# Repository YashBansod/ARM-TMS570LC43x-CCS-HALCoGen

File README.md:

# ARM-TMS570LC43x-CCS-HALCoGen
This repository contains all my practice codes/projects of Hercules TMS570LC43x Development Kit. The projects are made using embedded C on CCS 6 and HALCoGen.

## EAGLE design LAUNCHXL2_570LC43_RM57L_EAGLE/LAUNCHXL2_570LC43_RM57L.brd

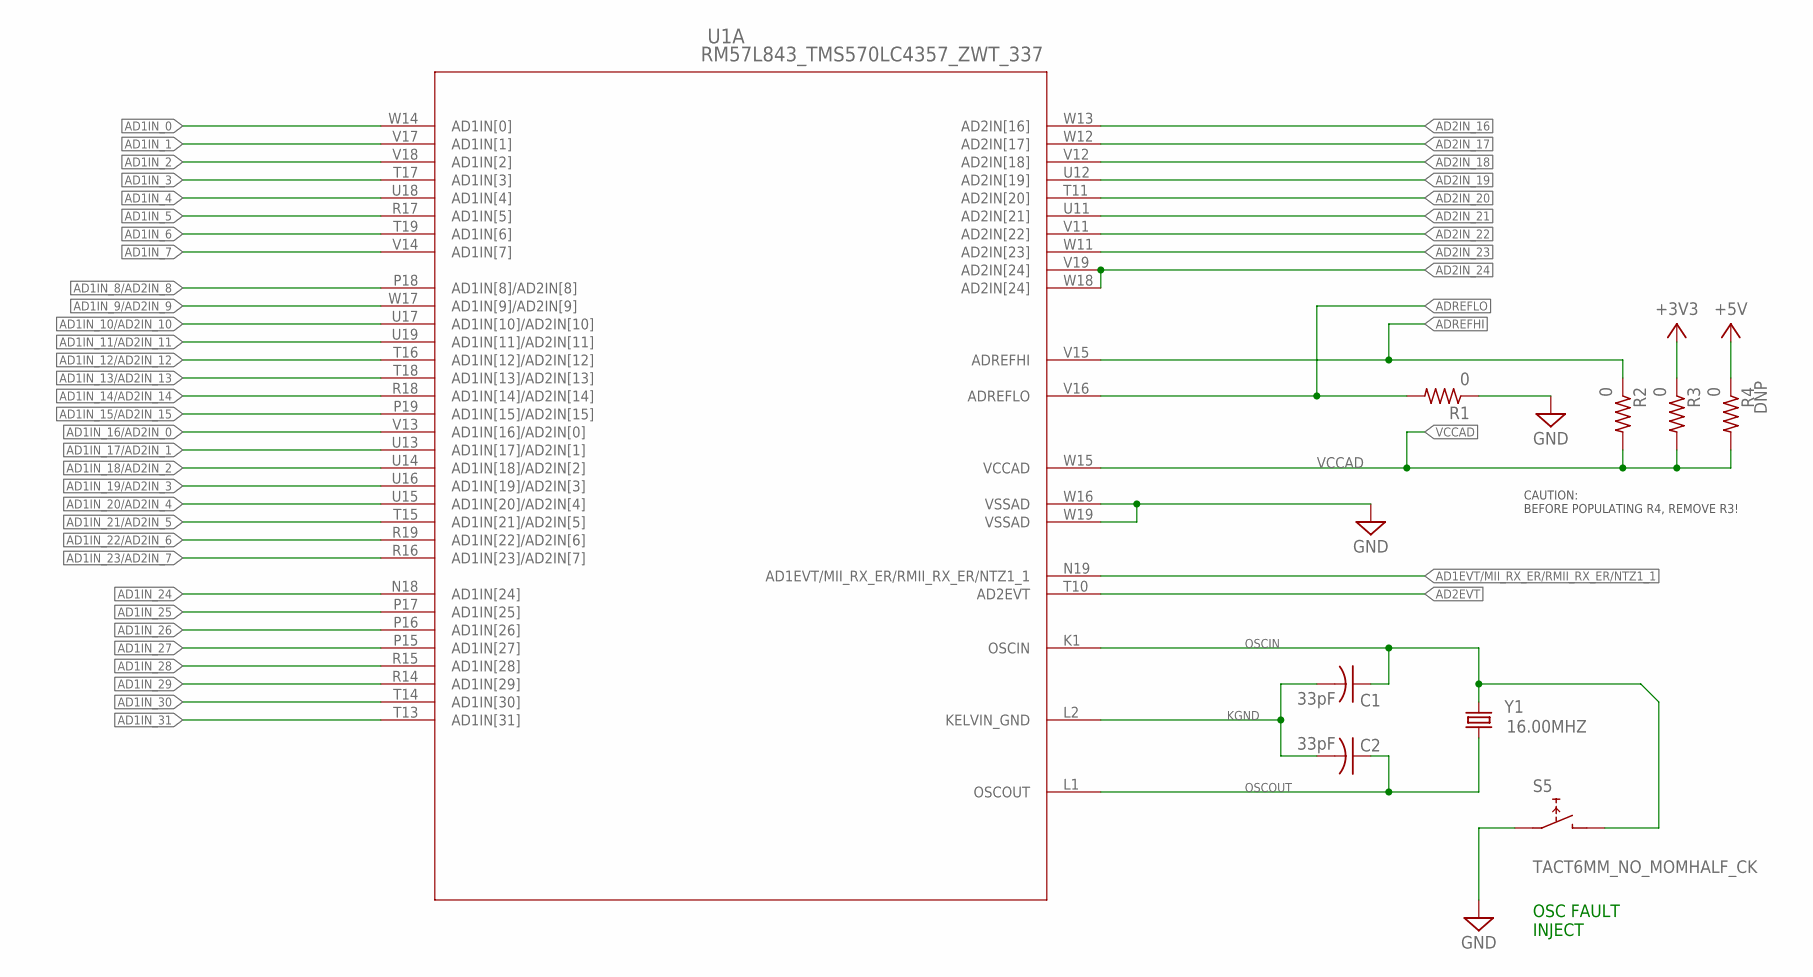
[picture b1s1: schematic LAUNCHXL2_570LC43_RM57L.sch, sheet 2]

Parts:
C1, C2: 33pF; C0201; PARTNO CC0201JRNPO8BN330
R1, R2, R3, R4: 0; R0201; PARTNO RC0201JR-070RL
S5: TACT6MM_NO_MOMHALF_CK; CK_PTS645_SMD; PARTNO PTS645SM43SMTR92 LFS
U1: RM57L843_TMS570LC4357_ZWT_337; ZWT337; PARTNO TMP5704357AZWTQQ1
Y1: 16.00MHZ; CSM-3X; PARTNO ECS-160-20-3X-TR

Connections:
+3V3: R3.1; also elsewhere on the board
+5V: R4.1; also elsewhere on the board
AD1EVT/MII_RX_ER/RMII_RX_ER/NTZ1_1: U1.N19 (AD1EVT/MII_RX_ER/RMII_RX_ER/NTZ1_1); also elsewhere on the board
AD1IN_0: U1.W14 (AD1IN[0]); also elsewhere on the board
AD1IN_1: U1.V17 (AD1IN[1]); also elsewhere on the board
AD1IN_2: U1.V18 (AD1IN[2]); also elsewhere on the board
AD1IN_3: U1.T17 (AD1IN[3]); also elsewhere on the board
AD1IN_4: U1.U18 (AD1IN[4]); also elsewhere on the board
AD1IN_5: U1.R17 (AD1IN[5]); also elsewhere on the board
AD1IN_6: U1.T19 (AD1IN[6]); also elsewhere on the board
AD1IN_7: U1.V14 (AD1IN[7]); also elsewhere on the board
AD1IN_8/AD2IN_8: U1.P18 (AD1IN[8]/AD2IN[8]); also elsewhere on the board
AD1IN_9/AD2IN_9: U1.W17 (AD1IN[9]/AD2IN[9]); also elsewhere on the board
AD1IN_10/AD2IN_10: U1.U17 (AD1IN[10]/AD2IN[10]); also elsewhere on the board
AD1IN_11/AD2IN_11: U1.U19 (AD1IN[11]/AD2IN[11]); also elsewhere on the board
AD1IN_12/AD2IN_12: U1.T16 (AD1IN[12]/AD2IN[12]); also elsewhere on the board
AD1IN_13/AD2IN_13: U1.T18 (AD1IN[13]/AD2IN[13]); also elsewhere on the board
AD1IN_14/AD2IN_14: U1.R18 (AD1IN[14]/AD2IN[14]); also elsewhere on the board
AD1IN_15/AD2IN_15: U1.P19 (AD1IN[15]/AD2IN[15]); also elsewhere on the board
AD1IN_16/AD2IN_0: U1.V13 (AD1IN[16]/AD2IN[0]); also elsewhere on the board
AD1IN_17/AD2IN_1: U1.U13 (AD1IN[17]/AD2IN[1]); also elsewhere on the board
AD1IN_18/AD2IN_2: U1.U14 (AD1IN[18]/AD2IN[2]); also elsewhere on the board
AD1IN_19/AD2IN_3: U1.U16 (AD1IN[19]/AD2IN[3]); also elsewhere on the board
AD1IN_20/AD2IN_4: U1.U15 (AD1IN[20]/AD2IN[4]); also elsewhere on the board
AD1IN_21/AD2IN_5: U1.T15 (AD1IN[21]/AD2IN[5]); also elsewhere on the board
AD1IN_22/AD2IN_6: U1.R19 (AD1IN[22]/AD2IN[6]); also elsewhere on the board
AD1IN_23/AD2IN_7: U1.R16 (AD1IN[23]/AD2IN[7]); also elsewhere on the board
AD1IN_24: U1.N18 (AD1IN[24]); also elsewhere on the board
AD1IN_25: U1.P17 (AD1IN[25]); also elsewhere on the board
AD1IN_26: U1.P16 (AD1IN[26]); also elsewhere on the board
AD1IN_27: U1.P15 (AD1IN[27]); also elsewhere on the board
AD1IN_28: U1.R15 (AD1IN[28]); also elsewhere on the board
AD1IN_29: U1.R14 (AD1IN[29]); also elsewhere on the board
AD1IN_30: U1.T14 (AD1IN[30]); also elsewhere on the board
AD1IN_31: U1.T13 (AD1IN[31]); also elsewhere on the board
AD2EVT: U1.T10 (AD2EVT); also elsewhere on the board
AD2IN_16: U1.W13 (AD2IN[16]); also elsewhere on the board
AD2IN_17: U1.W12 (AD2IN[17]); also elsewhere on the board
AD2IN_18: U1.V12 (AD2IN[18]); also elsewhere on the board
AD2IN_19: U1.U12 (AD2IN[19]); also elsewhere on the board
AD2IN_20: U1.T11 (AD2IN[20]); also elsewhere on the board
AD2IN_21: U1.U11 (AD2IN[21]); also elsewhere on the board
AD2IN_22: U1.V11 (AD2IN[22]); also elsewhere on the board
AD2IN_23: U1.W11 (AD2IN[23]); also elsewhere on the board
AD2IN_24: U1.V19 (AD2IN[24]), U1.W18 (AD2IN[24]); also elsewhere on the board
ADREFHI: R2.1, U1.V15 (ADREFHI); also elsewhere on the board
ADREFLO: R1.2, U1.V16 (ADREFLO); also elsewhere on the board
GND: R1.1, S5.1 (12), U1.W16 (VSSAD), U1.W19 (VSSAD); also elsewhere on the board
KGND: C1.2, C2.2, U1.L2 (KELVIN_GND)
OSCIN: C1.1, S5.3 (34), U1.K1 (OSCIN), Y1.2
OSCOUT: C2.1, U1.L1 (OSCOUT), Y1.1
VCCAD: R2.2, R3.2, R4.2, U1.W15 (VCCAD); also elsewhere on the board

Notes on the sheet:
OSC FAULT INJECT
CAUTION: BEFORE POPULATING R4, REMOVE R3!

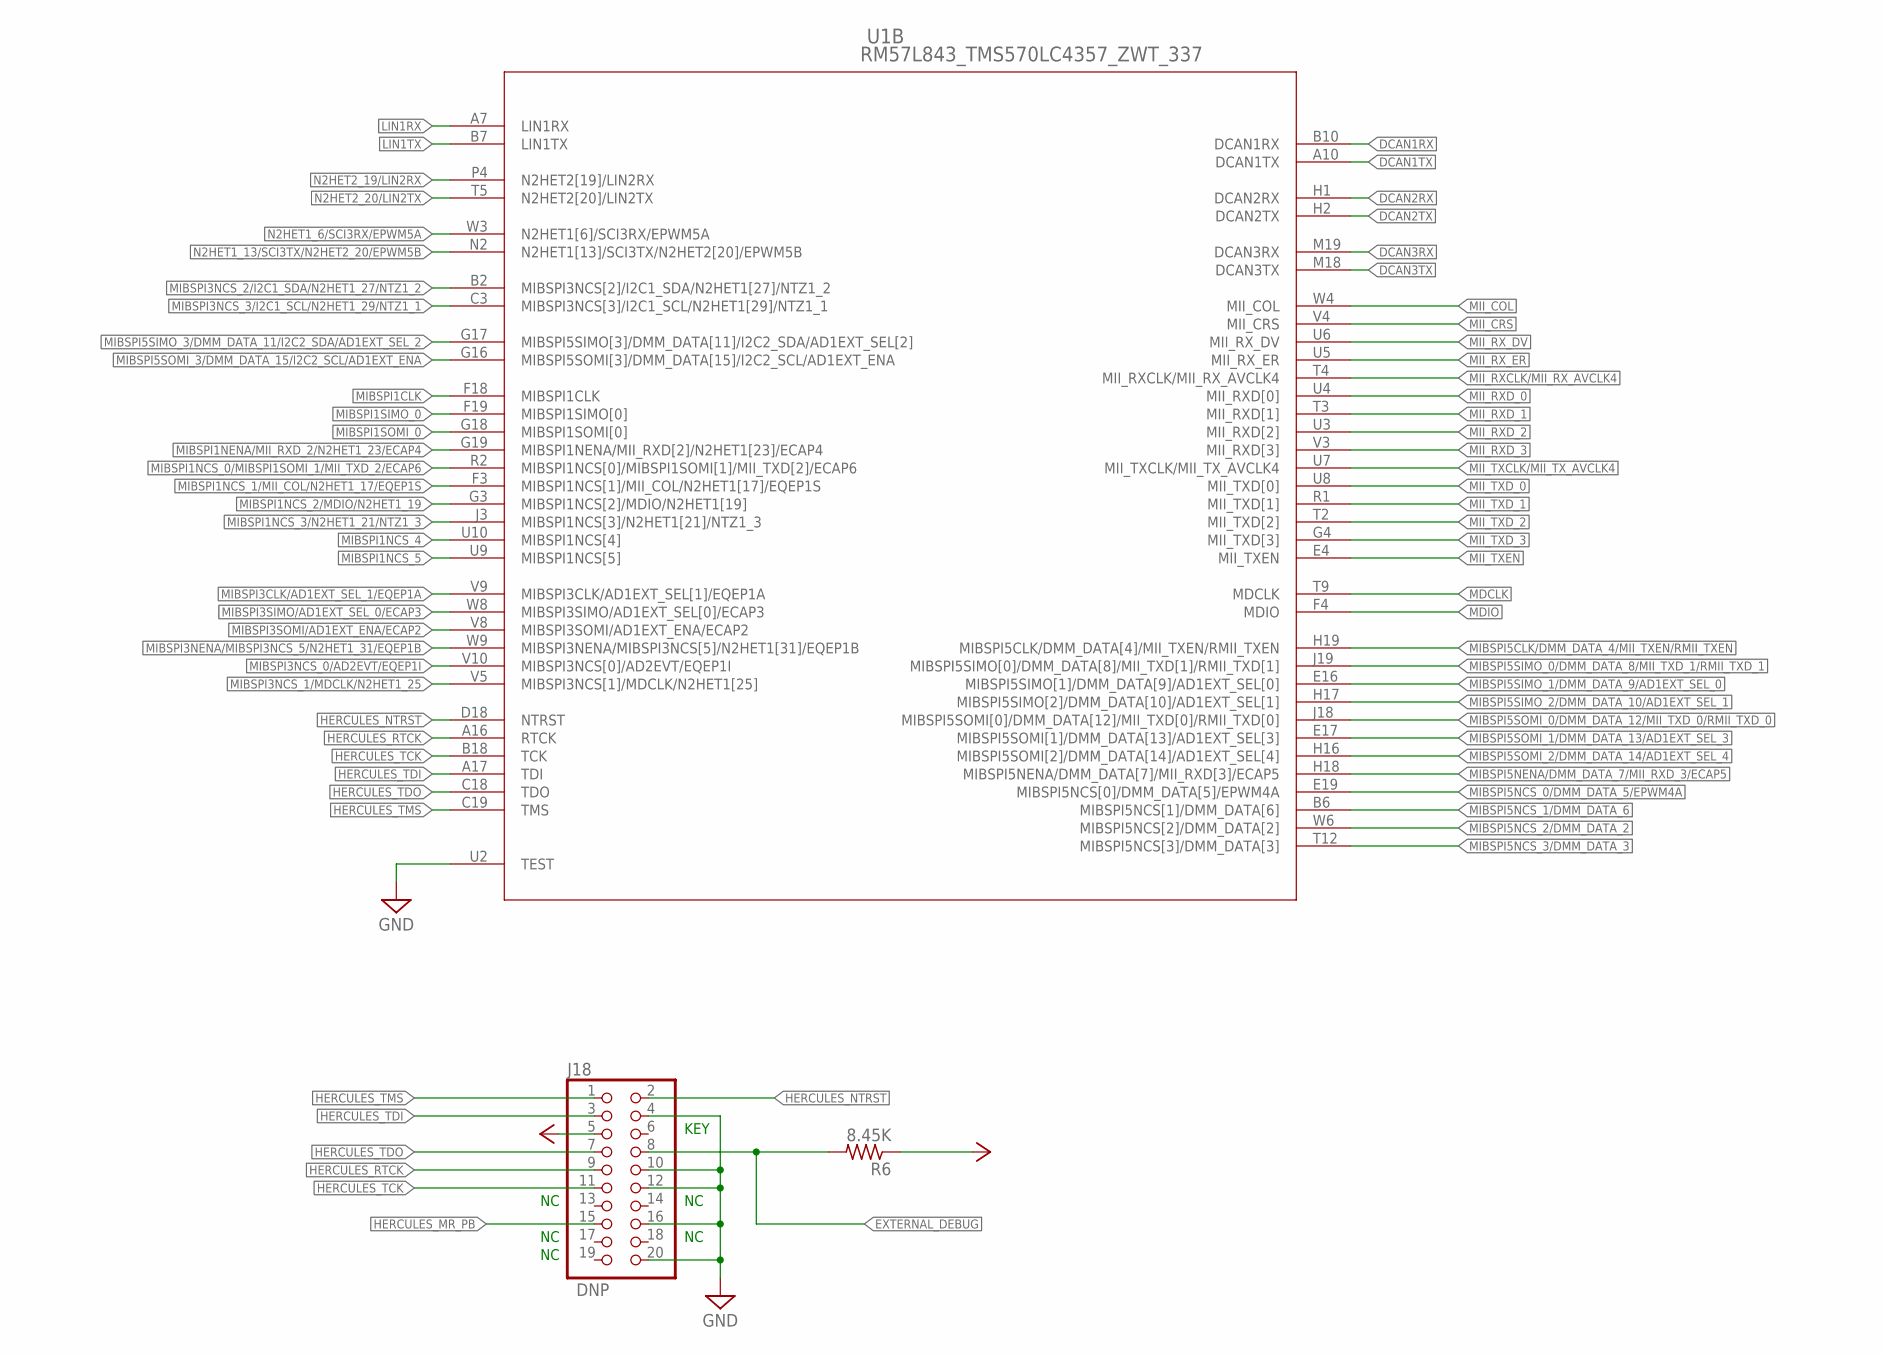
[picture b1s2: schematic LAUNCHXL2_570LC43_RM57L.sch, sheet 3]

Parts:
J18: PINHD-2X10SAMTEC-FTR-110-51-S-D-06; SAMTEC-FTR-110-51-S-D-06; PARTNO FTR-110-51-S-D-06
R6: 8.45K; R0201; PARTNO RC0603F8451CS
U1: RM57L843_TMS570LC4357_ZWT_337; ZWT337; PARTNO TMP5704357AZWTQQ1

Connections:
+3V3: J18.5, R6.1; also elsewhere on the board
DCAN1RX: U1.B10 (DCAN1RX); also elsewhere on the board
DCAN1TX: U1.A10 (DCAN1TX); also elsewhere on the board
DCAN2RX: U1.H1 (DCAN2RX); also elsewhere on the board
DCAN2TX: U1.H2 (DCAN2TX); also elsewhere on the board
DCAN3RX: U1.M19 (DCAN3RX); also elsewhere on the board
DCAN3TX: U1.M18 (DCAN3TX); also elsewhere on the board
EXTERNAL_DEBUG: J18.8, R6.2; also elsewhere on the board
GND: J18.4, J18.10, J18.12, J18.16, J18.20, U1.U2 (TEST); also elsewhere on the board
HERCULES_MR_PB: J18.15; also elsewhere on the board
HERCULES_NTRST: J18.2, U1.D18 (NTRST); also elsewhere on the board
HERCULES_RTCK: J18.9, U1.A16 (RTCK); also elsewhere on the board
HERCULES_TCK: J18.11, U1.B18 (TCK); also elsewhere on the board
HERCULES_TDI: J18.3, U1.A17 (TDI); also elsewhere on the board
HERCULES_TDO: J18.7, U1.C18 (TDO); also elsewhere on the board
HERCULES_TMS: J18.1, U1.C19 (TMS); also elsewhere on the board
LIN1RX: U1.A7 (LIN1RX); also elsewhere on the board
LIN1TX: U1.B7 (LIN1TX); also elsewhere on the board
MDCLK: U1.T9 (MDCLK); also elsewhere on the board
MDIO: U1.F4 (MDIO); also elsewhere on the board
MIBSPI1CLK: U1.F18 (MIBSPI1CLK); also elsewhere on the board
MIBSPI1NCS_0/MIBSPI1SOMI_1/MII_TXD_2/ECAP6: U1.R2 (MIBSPI1NCS[0]/MIBSPI1SOMI[1]/MII_TXD[2]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); also elsewhere on the board
MIBSPI1NCS_1/MII_COL/N2HET1_17/EQEP1S: U1.F3 (MIBSPI1NCS[1]/MII_COL/N2HET1[17]/EQEP1S); also elsewhere on the board
MIBSPI1NCS_2/MDIO/N2HET1_19: U1.G3 (MIBSPI1NCS[2]/MDIO/N2HET1[19]); also elsewhere on the board
MIBSPI1NCS_3/N2HET1_21/NTZ1_3: U1.J3 (MIBSPI1NCS[3]/N2HET1[21]/NTZ1_3); also elsewhere on the board
MIBSPI1NCS_4: U1.U10 (MIBSPI1NCS[4]); also elsewhere on the board
MIBSPI1NCS_5: U1.U9 (MIBSPI1NCS[5]); also elsewhere on the board
MIBSPI1NENA/MII_RXD_2/N2HET1_23/ECAP4: U1.G19 (MIBSPI1NENA/MII_RXD[2]/N2HET1[23]/ECAP4); also elsewhere on the board
MIBSPI1SIMO_0: U1.F19 (MIBSPI1SIMO[0]); also elsewhere on the board
MIBSPI1SOMI_0: U1.G18 (MIBSPI1SOMI[0]); also elsewhere on the board
MIBSPI3CLK/AD1EXT_SEL_1/EQEP1A: U1.V9 (MIBSPI3CLK/AD1EXT_SEL[1]/EQEP1A); also elsewhere on the board
MIBSPI3NCS_0/AD2EVT/EQEP1I: U1.V10 (MIBSPI3NCS[0]/AD2EVT/EQEP1I); also elsewhere on the board
MIBSPI3NCS_1/MDCLK/N2HET1_25: U1.V5 (MIBSPI3NCS[1]/MDCLK/N2HET1[25]); also elsewhere on the board
MIBSPI3NCS_2/I2C1_SDA/N2HET1_27/NTZ1_2: U1.B2 (MIBSPI3NCS[2]/I2C1_SDA/N2HET1[27]/NTZ1_2); also elsewhere on the board
MIBSPI3NCS_3/I2C1_SCL/N2HET1_29/NTZ1_1: U1.C3 (MIBSPI3NCS[3]/I2C1_SCL/N2HET1[29]/NTZ1_1); also elsewhere on the board
MIBSPI3NENA/MIBSPI3NCS_5/N2HET1_31/EQEP1B: U1.W9 (MIBSPI3NENA/MIBSPI3NCS[5]/N2HET1[31]/EQ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); also elsewhere on the board
MIBSPI3SIMO/AD1EXT_SEL_0/ECAP3: U1.W8 (MIBSPI3SIMO/AD1EXT_SEL[0]/ECAP3); also elsewhere on the board
MIBSPI3SOMI/AD1EXT_ENA/ECAP2: U1.V8 (MIBSPI3SOMI/AD1EXT_ENA/ECAP2); also elsewhere on the board
MIBSPI5CLK/DMM_DATA_4/MII_TXEN/RMII_TXEN: U1.H19 (MIBSPI5CLK/DMM_DATA[4]/MII_TXEN/RMII_TX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); also elsewhere on the board
MIBSPI5NCS_0/DMM_DATA_5/EPWM4A: U1.E19 (MIBSPI5NCS[0]/DMM_DATA[5]/EPWM4A); also elsewhere on the board
MIBSPI5NCS_1/DMM_DATA_6: U1.B6 (MIBSPI5NCS[1]/DMM_DATA[6]); also elsewhere on the board
MIBSPI5NCS_2/DMM_DATA_2: U1.W6 (MIBSPI5NCS[2]/DMM_DATA[2]); also elsewhere on the board
MIBSPI5NCS_3/DMM_DATA_3: U1.T12 (MIBSPI5NCS[3]/DMM_DATA[3]); also elsewhere on the board
MIBSPI5NENA/DMM_DATA_7/MII_RXD_3/ECAP5: U1.H18 (MIBSPI5NENA/DMM_DATA[7]/MII_RXD[3]/ECAP5); also elsewhere on the board
MIBSPI5SIMO_0/DMM_DATA_8/MII_TXD_1/RMII_TXD_1: U1.J19 (MIBSPI5SIMO[0]/DMM_DATA[8]/MII_TXD[1]/R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); also elsewhere on the board
MIBSPI5SIMO_1/DMM_DATA_9/AD1EXT_SEL_0: U1.E16 (MIBSPI5SIMO[1]/DMM_DATA[9]/AD1EXT_SEL[0]); also elsewhere on the board
MIBSPI5SIMO_2/DMM_DATA_10/AD1EXT_SEL_1: U1.H17 (MIBSPI5SIMO[2]/DMM_DATA[10]/AD1EXT_SEL[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); also elsewhere on the board
MIBSPI5SIMO_3/DMM_DATA_11/I2C2_SDA/AD1EXT_SEL_2: U1.G17 (MIBSPI5SIMO[3]/DMM_DATA[11]/I2C2_SDA/AD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); also elsewhere on the board
MIBSPI5SOMI_0/DMM_DATA_12/MII_TXD_0/RMII_TXD_0: U1.J18 (MIBSPI5SOMI[0]/DMM_DATA[12]/MII_TXD[0]/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); also elsewhere on the board
MIBSPI5SOMI_1/DMM_DATA_13/AD1EXT_SEL_3: U1.E17 (MIBSPI5SOMI[1]/DMM_DATA[13]/AD1EXT_SEL[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); also elsewhere on the board
MIBSPI5SOMI_2/DMM_DATA_14/AD1EXT_SEL_4: U1.H16 (MIBSPI5SOMI[2]/DMM_DATA[14]/AD1EXT_SEL[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); also elsewhere on the board
MIBSPI5SOMI_3/DMM_DATA_15/I2C2_SCL/AD1EXT_ENA: U1.G16 (MIBSPI5SOMI[3]/DMM_DATA[15]/I2C2_SCL/AD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); also elsewhere on the board
MII_COL: U1.W4 (MII_COL); also elsewhere on the board
MII_CRS: U1.V4 (MII_CRS); also elsewhere on the board
MII_RXCLK/MII_RX_AVCLK4: U1.T4 (MII_RXCLK/MII_RX_AVCLK4); also elsewhere on the board
MII_RXD_0: U1.U4 (MII_RXD[0]); also elsewhere on the board
MII_RXD_1: U1.T3 (MII_RXD[1]); also elsewhere on the board
MII_RXD_2: U1.U3 (MII_RXD[2]); also elsewhere on the board
MII_RXD_3: U1.V3 (MII_RXD[3]); also elsewhere on the board
MII_RX_DV: U1.U6 (MII_RX_DV); also elsewhere on the board
MII_RX_ER: U1.U5 (MII_RX_ER); also elsewhere on the board
MII_TXCLK/MII_TX_AVCLK4: U1.U7 (MII_TXCLK/MII_TX_AVCLK4); also elsewhere on the board
MII_TXD_0: U1.U8 (MII_TXD[0]); also elsewhere on the board
MII_TXD_1: U1.R1 (MII_TXD[1]); also elsewhere on the board
MII_TXD_2: U1.T2 (MII_TXD[2]); also elsewhere on the board
MII_TXD_3: U1.G4 (MII_TXD[3]); also elsewhere on the board
MII_TXEN: U1.E4 (MII_TXEN); also elsewhere on the board
N2HET1_6/SCI3RX/EPWM5A: U1.W3 (N2HET1[6]/SCI3RX/EPWM5A); also elsewhere on the board
N2HET1_13/SCI3TX/N2HET2_20/EPWM5B: U1.N2 (N2HET1[13]/SCI3TX/N2HET2[20]/EPWM5B); also elsewhere on the board
N2HET2_19/LIN2RX: U1.P4 (N2HET2[19]/LIN2RX); also elsewhere on the board
N2HET2_20/LIN2TX: U1.T5 (N2HET2[20]/LIN2TX); also elsewhere on the board

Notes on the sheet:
KEY

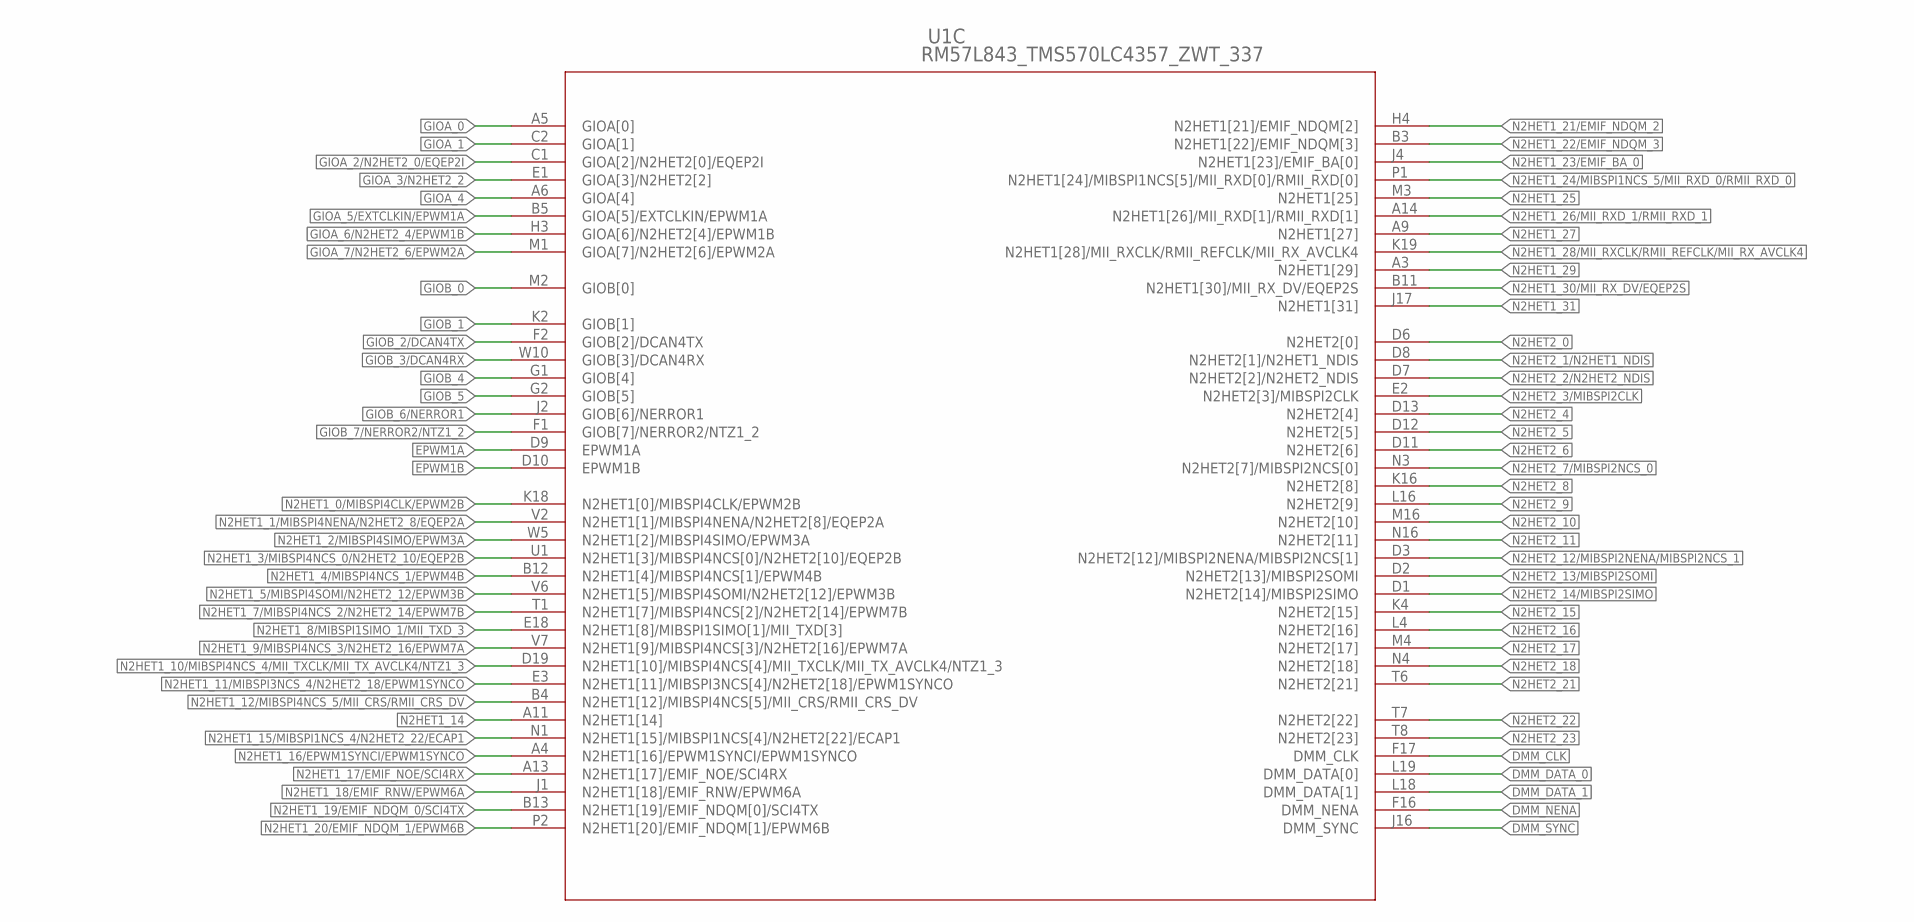
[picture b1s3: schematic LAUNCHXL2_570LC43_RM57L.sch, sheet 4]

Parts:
U1: RM57L843_TMS570LC4357_ZWT_337; ZWT337; PARTNO TMP5704357AZWTQQ1

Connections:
DMM_CLK: U1.F17 (DMM_CLK); also elsewhere on the board
DMM_DATA_0: U1.L19 (DMM_DATA[0]); also elsewhere on the board
DMM_DATA_1: U1.L18 (DMM_DATA[1]); also elsewhere on the board
DMM_NENA: U1.F16 (DMM_NENA); also elsewhere on the board
DMM_SYNC: U1.J16 (DMM_SYNC); also elsewhere on the board
EPWM1A: U1.D9 (EPWM1A); also elsewhere on the board
EPWM1B: U1.D10 (EPWM1B); also elsewhere on the board
GIOA_0: U1.A5 (GIOA[0]); also elsewhere on the board
GIOA_1: U1.C2 (GIOA[1]); also elsewhere on the board
GIOA_2/N2HET2_0/EQEP2I: U1.C1 (GIOA[2]/N2HET2[0]/EQEP2I); also elsewhere on the board
GIOA_3/N2HET2_2: U1.E1 (GIOA[3]/N2HET2[2]); also elsewhere on the board
GIOA_4: U1.A6 (GIOA[4]); also elsewhere on the board
GIOA_5/EXTCLKIN/EPWM1A: U1.B5 (GIOA[5]/EXTCLKIN/EPWM1A); also elsewhere on the board
GIOA_6/N2HET2_4/EPWM1B: U1.H3 (GIOA[6]/N2HET2[4]/EPWM1B); also elsewhere on the board
GIOA_7/N2HET2_6/EPWM2A: U1.M1 (GIOA[7]/N2HET2[6]/EPWM2A); also elsewhere on the board
GIOB_0: U1.M2 (GIOB[0]); also elsewhere on the board
GIOB_1: U1.K2 (GIOB[1]); also elsewhere on the board
GIOB_2/DCAN4TX: U1.F2 (GIOB[2]/DCAN4TX); also elsewhere on the board
GIOB_3/DCAN4RX: U1.W10 (GIOB[3]/DCAN4RX); also elsewhere on the board
GIOB_4: U1.G1 (GIOB[4]); also elsewhere on the board
GIOB_5: U1.G2 (GIOB[5]); also elsewhere on the board
GIOB_6/NERROR1: U1.J2 (GIOB[6]/NERROR1); also elsewhere on the board
GIOB_7/NERROR2/NTZ1_2: U1.F1 (GIOB[7]/NERROR2/NTZ1_2); also elsewhere on the board
N2HET1_0/MIBSPI4CLK/EPWM2B: U1.K18 (N2HET1[0]/MIBSPI4CLK/EPWM2B); also elsewhere on the board
N2HET1_1/MIBSPI4NENA/N2HET2_8/EQEP2A: U1.V2 (N2HET1[1]/MIBSPI4NENA/N2HET2[8]/EQEP2A); also elsewhere on the board
N2HET1_2/MIBSPI4SIMO/EPWM3A: U1.W5 (N2HET1[2]/MIBSPI4SIMO/EPWM3A); also elsewhere on the board
N2HET1_3/MIBSPI4NCS_0/N2HET2_10/EQEP2B: U1.U1 (N2HET1[3]/MIBSPI4NCS[0]/N2HET2[10]/EQEP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); also elsewhere on the board
N2HET1_4/MIBSPI4NCS_1/EPWM4B: U1.B12 (N2HET1[4]/MIBSPI4NCS[1]/EPWM4B); also elsewhere on the board
N2HET1_5/MIBSPI4SOMI/N2HET2_12/EPWM3B: U1.V6 (N2HET1[5]/MIBSPI4SOMI/N2HET2[12]/EPWM3B); also elsewhere on the board
N2HET1_7/MIBSPI4NCS_2/N2HET2_14/EPWM7B: U1.T1 (N2HET1[7]/MIBSPI4NCS[2]/N2HET2[14]/EPWM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); also elsewhere on the board
N2HET1_8/MIBSPI1SIMO_1/MII_TXD_3: U1.E18 (N2HET1[8]/MIBSPI1SIMO[1]/MII_TXD[3]); also elsewhere on the board
N2HET1_9/MIBSPI4NCS_3/N2HET2_16/EPWM7A: U1.V7 (N2HET1[9]/MIBSPI4NCS[3]/N2HET2[16]/EPWM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); also elsewhere on the board
N2HET1_10/MIBSPI4NCS_4/MII_TXCLK/MII_TX_AVCLK4/NTZ1_3: U1.D19 (N2HET1[10]/MIBSPI4NCS[4]/MII_TXCLK/MII_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); also elsewhere on the board
N2HET1_11/MIBSPI3NCS_4/N2HET2_18/EPWM1SYNCO: U1.E3 (N2HET1[11]/MIBSPI3NCS[4]/N2HET2[18]/EPW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); also elsewhere on the board
N2HET1_12/MIBSPI4NCS_5/MII_CRS/RMII_CRS_DV: U1.B4 (N2HET1[12]/MIBSPI4NCS[5]/MII_CRS/RMII_C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); also elsewhere on the board
N2HET1_14: U1.A11 (N2HET1[14]); also elsewhere on the board
N2HET1_15/MIBSPI1NCS_4/N2HET2_22/ECAP1: U1.N1 (N2HET1[15]/MIBSPI1NCS[4]/N2HET2[22]/ECA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); also elsewhere on the board
N2HET1_16/EPWM1SYNCI/EPWM1SYNCO: U1.A4 (N2HET1[16]/EPWM1SYNCI/EPWM1SYNCO); also elsewhere on the board
N2HET1_17/EMIF_NOE/SCI4RX: U1.A13 (N2HET1[17]/EMIF_NOE/SCI4RX); also elsewhere on the board
N2HET1_18/EMIF_RNW/EPWM6A: U1.J1 (N2HET1[18]/EMIF_RNW/EPWM6A); also elsewhere on the board
N2HET1_19/EMIF_NDQM_0/SCI4TX: U1.B13 (N2HET1[19]/EMIF_NDQM[0]/SCI4TX); also elsewhere on the board
N2HET1_20/EMIF_NDQM_1/EPWM6B: U1.P2 (N2HET1[20]/EMIF_NDQM[1]/EPWM6B); also elsewhere on the board
N2HET1_21/EMIF_NDQM_2: U1.H4 (N2HET1[21]/EMIF_NDQM[2]); also elsewhere on the board
N2HET1_22/EMIF_NDQM_3: U1.B3 (N2HET1[22]/EMIF_NDQM[3]); also elsewhere on the board
N2HET1_23/EMIF_BA_0: U1.J4 (N2HET1[23]/EMIF_BA[0]); also elsewhere on the board
N2HET1_24/MIBSPI1NCS_5/MII_RXD_0/RMII_RXD_0: U1.P1 (N2HET1[24]/MIBSPI1NCS[5]/MII_RXD[0]/RMI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); also elsewhere on the board
N2HET1_25: U1.M3 (N2HET1[25]); also elsewhere on the board
N2HET1_26/MII_RXD_1/RMII_RXD_1: U1.A14 (N2HET1[26]/MII_RXD[1]/RMII_RXD[1]); also elsewhere on the board
N2HET1_27: U1.A9 (N2HET1[27]); also elsewhere on the board
N2HET1_28/MII_RXCLK/RMII_REFCLK/MII_RX_AVCLK4: U1.K19 (N2HET1[28]/MII_RXCLK/RMII_REFCLK/MII_RX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); also elsewhere on the board
N2HET1_29: U1.A3 (N2HET1[29]); also elsewhere on the board
N2HET1_30/MII_RX_DV/EQEP2S: U1.B11 (N2HET1[30]/MII_RX_DV/EQEP2S); also elsewhere on the board
N2HET1_31: U1.J17 (N2HET1[31]); also elsewhere on the board
N2HET2_0: U1.D6 (N2HET2[0]); also elsewhere on the board
N2HET2_1/N2HET1_NDIS: U1.D8 (N2HET2[1]/N2HET1_NDIS); also elsewhere on the board
N2HET2_2/N2HET2_NDIS: U1.D7 (N2HET2[2]/N2HET2_NDIS); also elsewhere on the board
N2HET2_3/MIBSPI2CLK: U1.E2 (N2HET2[3]/MIBSPI2CLK); also elsewhere on the board
N2HET2_4: U1.D13 (N2HET2[4]); also elsewhere on the board
N2HET2_5: U1.D12 (N2HET2[5]); also elsewhere on the board
N2HET2_6: U1.D11 (N2HET2[6]); also elsewhere on the board
N2HET2_7/MIBSPI2NCS_0: U1.N3 (N2HET2[7]/MIBSPI2NCS[0]); also elsewhere on the board
N2HET2_8: U1.K16 (N2HET2[8]); also elsewhere on the board
N2HET2_9: U1.L16 (N2HET2[9]); also elsewhere on the board
N2HET2_10: U1.M16 (N2HET2[10]); also elsewhere on the board
N2HET2_11: U1.N16 (N2HET2[11]); also elsewhere on the board
N2HET2_12/MIBSPI2NENA/MIBSPI2NCS_1: U1.D3 (N2HET2[12]/MIBSPI2NENA/MIBSPI2NCS[1]); also elsewhere on the board
N2HET2_13/MIBSPI2SOMI: U1.D2 (N2HET2[13]/MIBSPI2SOMI); also elsewhere on the board
N2HET2_14/MIBSPI2SIMO: U1.D1 (N2HET2[14]/MIBSPI2SIMO); also elsewhere on the board
N2HET2_15: U1.K4 (N2HET2[15]); also elsewhere on the board
N2HET2_16: U1.L4 (N2HET2[16]); also elsewhere on the board
N2HET2_17: U1.M4 (N2HET2[17]); also elsewhere on the board
N2HET2_18: U1.N4 (N2HET2[18]); also elsewhere on the board
N2HET2_21: U1.T6 (N2HET2[21]); also elsewhere on the board
N2HET2_22: U1.T7 (N2HET2[22]); also elsewhere on the board
N2HET2_23: U1.T8 (N2HET2[23]); also elsewhere on the board

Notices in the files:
LAUNCHXL2_570LC43_RM57L_EAGLE/LAUNCHXL2_570LC43_RM57L.brd:
(C) 2014-2015
